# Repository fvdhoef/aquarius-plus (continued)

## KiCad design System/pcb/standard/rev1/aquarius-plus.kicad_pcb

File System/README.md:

# Aquarius+ System
This directory contains:
- [Schematic and PCB](pcb/)
- [FPGA firmware](fpga_cores/)
- [ESP32 firmware](esp32/)
- [ROM extensions source code](rom_src/aqplus_rom/)
- [Emulator source code](emulator/)
- [Documentation](docs/)

And some other stuff not mentioned in the list.

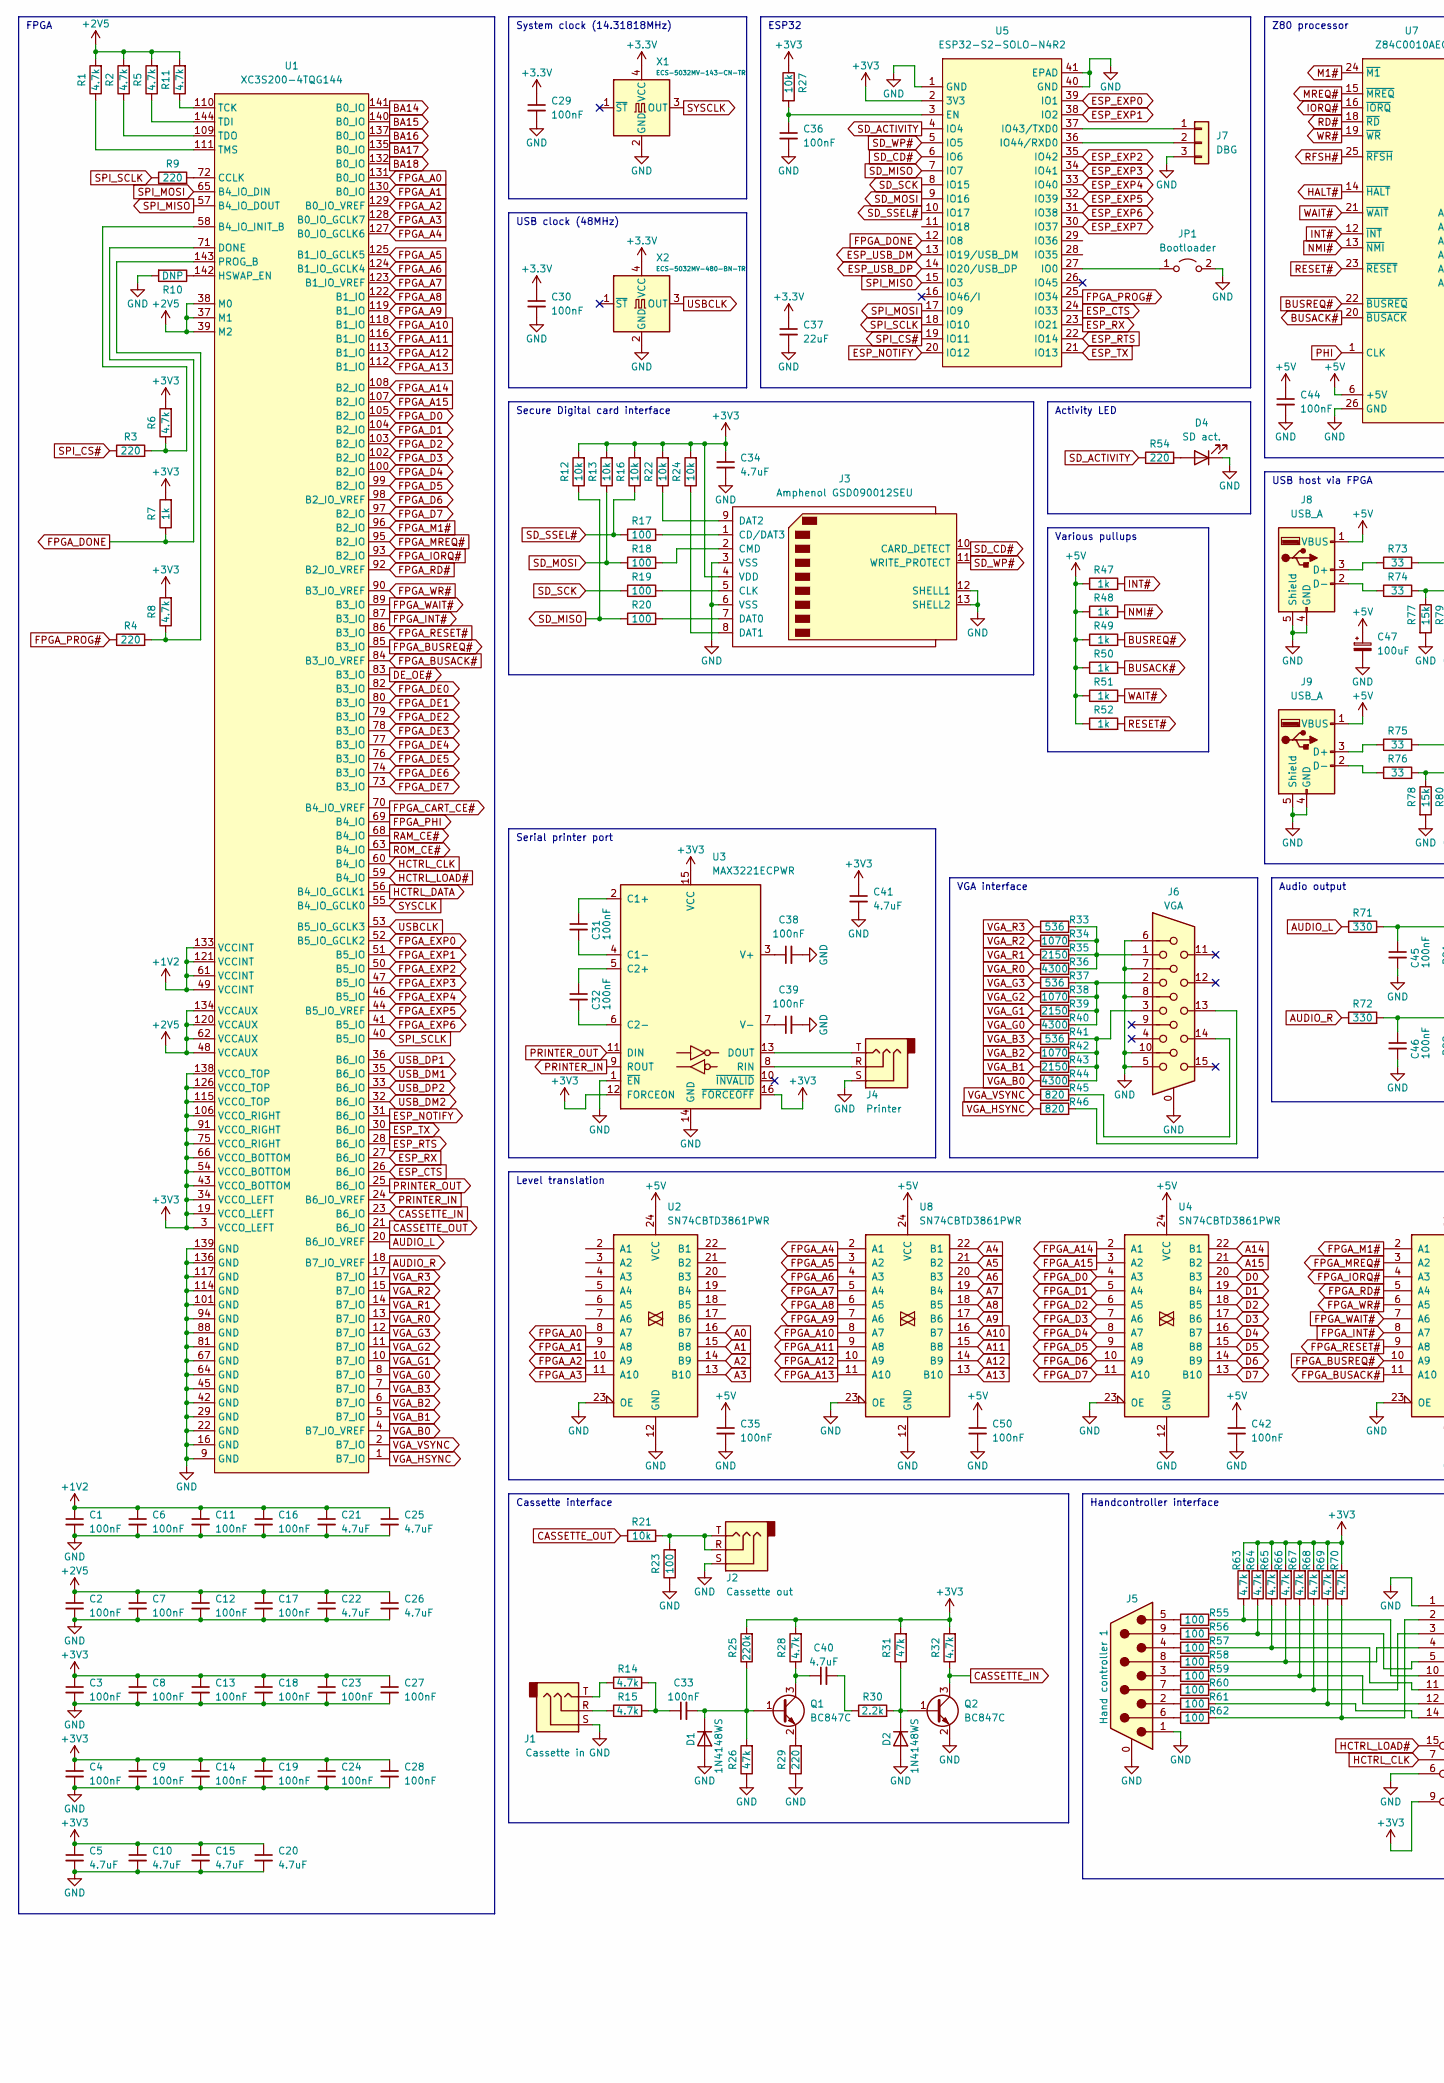
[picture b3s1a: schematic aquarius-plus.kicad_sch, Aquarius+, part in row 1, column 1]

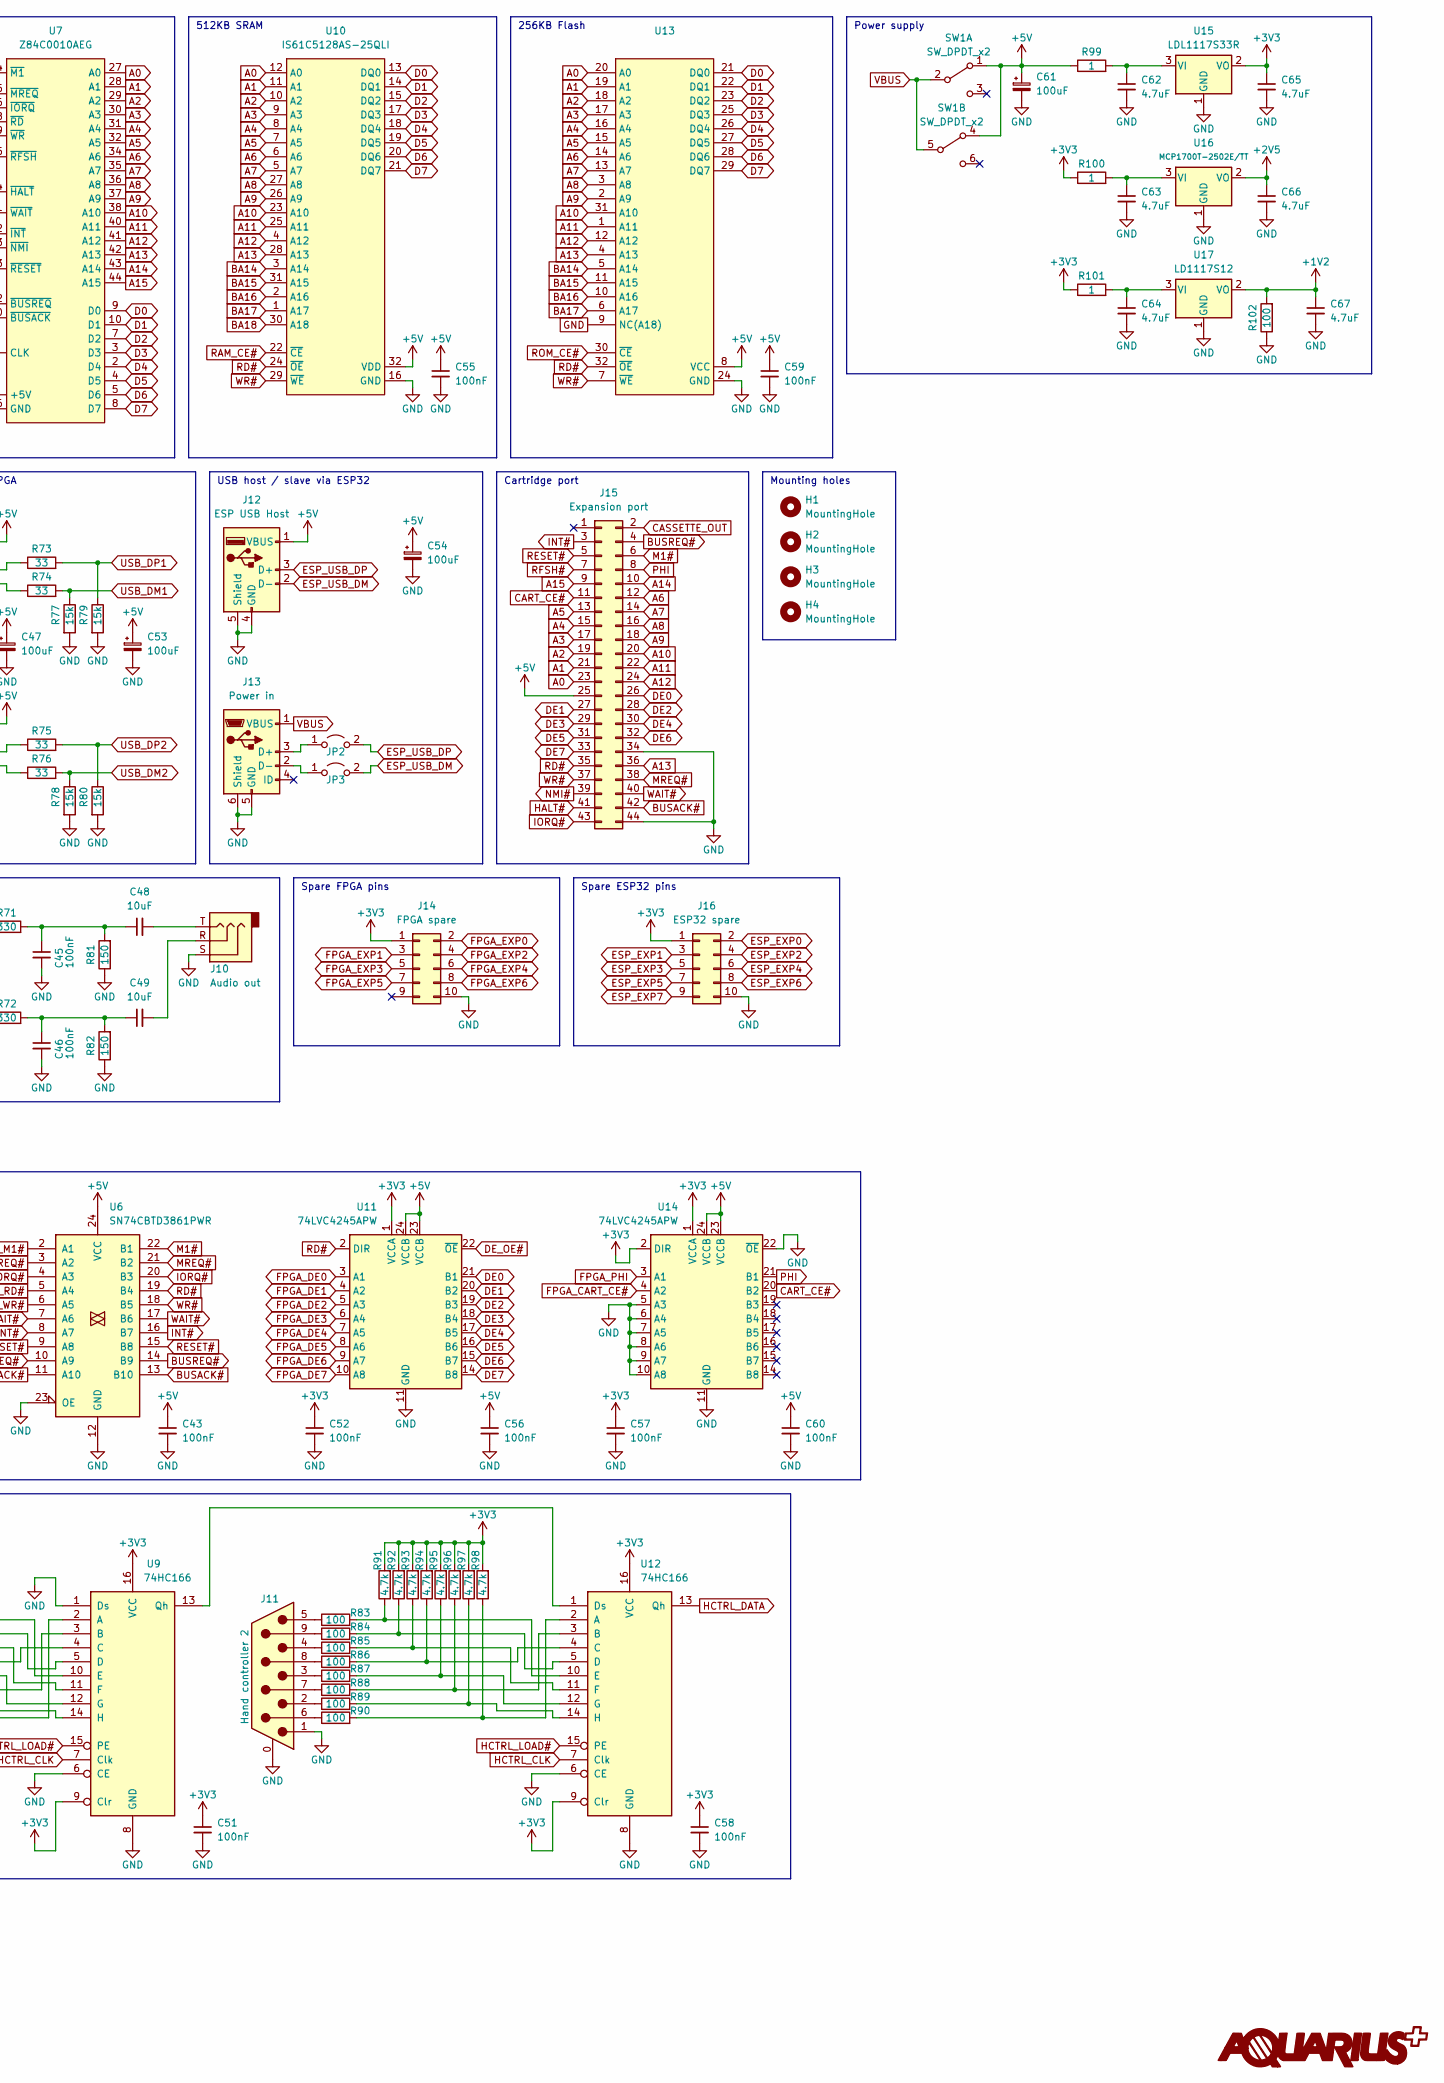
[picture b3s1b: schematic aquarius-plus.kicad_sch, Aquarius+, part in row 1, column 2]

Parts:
C1, C2, C3, C4, C6, C7, C8, C9, C11, C12, C13, C14, C16, C17, C18, C19, C23, C24, C27, C28, C29, C30, C31, C32, C33, C35, C36, C38, C39, C42, C43, C44, C45, C46, C50, C51, C52, C55, C56, C57, C58, C59, C60: 100nF; C_0603_1608Metric
C5, C10, C15, C20, C21, C22, C25, C26, C34, C40, C41, C62, C63, C64, C65, C66, C67: 4.7uF; C_0603_1608Metric
C37: 22uF; C_1206_3216Metric
C47, C53, C54, C61: 100uF; CP_Elec_6.3x7.7
C48, C49: 10uF; C_0805_2012Metric
D1, D2: 1N4148WS; D_SOD-323_HandSoldering
D4: SD act.; LED_D3.0mm_Horizontal_O1.27mm_Z2.0mm
H1, H2, H3, H4: MountingHole; MountingHole_3.2mm_M3
J1: Cassette in; Jack_3.5mm_CUI_SJ-3523-SMT_Horizontal
J2: Cassette out; Jack_3.5mm_CUI_SJ-3523-SMT_Horizontal
J3: Amphenol GSD090012SEU; SD_TE_2041021
J4: Printer; Jack_3.5mm_CUI_SJ-3523-SMT_Horizontal
J5: Hand controller 1; DSUB-9_Male_Horizontal_P2.77x2.84mm_EdgePinOffset9.90mm_Hou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
J6: VGA; ICD15S13E4GV00LF
J7: DBG; PinHeader_1x03_P2.54mm_Vertical
J8, J9: USB_A; USB_A_Molex_67643_Horizontal
J10: Audio out; Jack_3.5mm_CUI_SJ-3523-SMT_Horizontal
J11: Hand controller 2; DSUB-9_Male_Horizontal_P2.77x2.84mm_EdgePinOffset9.90mm_Hou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
J12: ESP USB Host; USB_A_Molex_67643_Horizontal
J13: Power in; 10118193-0001LF
J14: FPGA spare; PinHeader_2x05_P2.54mm_Vertical
J15: Expansion port; CR22A-44D-2.54DSA(70)
J16: ESP32 spare; PinHeader_2x05_P2.54mm_Vertical
JP1: Bootloader; PinHeader_1x02_P2.54mm_Vertical
JP2, JP3: USB; PinHeader_1x02_P2.54mm_Vertical
Q1, Q2: BC847C; SOT-23
R1, R2, R5, R6, R8, R11, R14, R15, R28, R32, R63, R64, R65, R66, R67, R68, R69, R70, R91, R92, R93, R94, R95, R96, R97, R98: 4.7k; R_0603_1608Metric
R3, R4, R9, R29, R54: 220; R_0603_1608Metric
R7, R47, R48, R49, R50, R51, R52: 1k; R_0603_1608Metric
R10: DNP; R_0603_1608Metric
R12, R13, R16, R21, R22, R24, R27: 10k; R_0603_1608Metric
R17, R18, R19, R20, R23, R55, R56, R57, R58, R59, R60, R61, R62, R83, R84, R85, R86, R87, R88, R89, R90, R102: 100; R_0603_1608Metric
R25: 220k; R_0603_1608Metric
R26, R31: 47k; R_0603_1608Metric
R30: 2.2k; R_0603_1608Metric
R33, R37, R41: 536; R_0603_1608Metric
R34, R38, R42: 1070; R_0603_1608Metric
R35, R39, R43: 2150; R_0603_1608Metric
R36, R40, R44: 4300; R_0603_1608Metric
R45, R46: 820; R_0603_1608Metric
R71, R72: 330; R_0603_1608Metric
R73, R74, R75, R76: 33; R_0603_1608Metric
R77, R78, R79, R80: 15k; R_0603_1608Metric
R81, R82: 150; R_0603_1608Metric
R99, R100, R101: 1; R_0603_1608Metric
SW1: SW_DPDT_x2; SW_E-Switch_EG2219_DPDT_Angled
U1: XC3S200-4TQG144; TQFP-144_20x20mm_P0.5mm
U2, U4, U6, U8: SN74CBTD3861PWR; TSSOP-24_4.4x7.8mm_P0.65mm
U3: MAX3221ECPWR; TSSOP-16_4.4x5mm_P0.65mm
U5: ESP32-S2-SOLO-N4R2
U7: Z84C0010AEG; LQFP-44_10x10mm_P0.8mm
U9, U12: 74HC166; SOIC-16_3.9x9.9mm_P1.27mm
U10: IS61C5128AS-25QLI; SSOP-32_11.305x20.495mm_P1.27mm
U11, U14: 74LVC4245APW; TSSOP-24_4.4x7.8mm_P0.65mm
U13: (no value)
U15: LDL1117S33R; SOT-223-3_TabPin2
U16: MCP1700T-2502E/TT; SOT-23
U17: LD1117S12; SOT-223-3_TabPin2
X1: ECS-5032MV-143-CN-TR; Oscillator_SMD_SeikoEpson_SG8002LB-4Pin_5.0x3.2mm
X2: ECS-5032MV-480-BN-TR; Oscillator_SMD_SeikoEpson_SG8002LB-4Pin_5.0x3.2mm

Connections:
+1V2: C1.1, C6.1, C11.1, C16.1, C21.1, C25.1, C67.1, R102.2, U1.49 (VCCINT), U1.61 (VCCINT), U1.121 (VCCINT), U1.133 (VCCINT), U17.2 (VO)
+2V5: C2.1, C7.1, C12.1, C17.1, C22.1, C26.1, C66.1, R1.2, R2.2, R5.2, R11.2, U1.37 (M1), U1.38 (M0), U1.39 (M2), U1.48 (VCCAUX), U1.62 (VCCAUX), U1.120 (VCCAUX), U1.134 (VCCAUX), U16.2 (VO)
+5V: C35.1, C42.1, C43.1, C44.1, C47.1, C50.1, C53.1, C54.1, C55.1, C56.1, C59.1, C60.1, C61.1, J8.1 (VBUS), J9.1 (VBUS), J12.1 (VBUS), J15.25, R47.1, R48.1, R49.1, R50.1, R51.1, R52.1, R99.1, SW1.1 (A), SW1.4 (A), U2.24 (VCC), U4.24 (VCC), U6.24 (VCC), U7.6 (+5V), U8.24 (VCC), U10.32 (VDD), U11.23 (VCCB), U11.24 (VCCB), U13.8 (VCC), U14.23 (VCCB), U14.24 (VCCB)
A0: J15.23, U2.16 (B7), U7.27 (A0), U10.12 (A0), U13.20 (A0)
A1: J15.21, U2.15 (B8), U7.28 (A1), U10.11 (A1), U13.19 (A1)
A2: J15.19, U2.14 (B9), U7.29 (A2), U10.10 (A2), U13.18 (A2)
A3: J15.17, U2.13 (B10), U7.30 (A3), U10.9 (A3), U13.17 (A3)
A4: J15.15, U7.31 (A4), U8.22 (B1), U10.8 (A4), U13.16 (A4)
A5: J15.13, U7.32 (A5), U8.21 (B2), U10.7 (A5), U13.15 (A5)
A6: J15.12, U7.34 (A6), U8.20 (B3), U10.6 (A6), U13.14 (A6)
A7: J15.14, U7.35 (A7), U8.19 (B4), U10.5 (A7), U13.13 (A7)
A8: J15.16, U7.36 (A8), U8.18 (B5), U10.27 (A8), U13.3 (A8)
A9: J15.18, U7.37 (A9), U8.17 (B6), U10.26 (A9), U13.2 (A9)
A10: J15.20, U7.38 (A10), U8.16 (B7), U10.23 (A10), U13.31 (A10)
A11: J15.22, U7.40 (A11), U8.15 (B8), U10.25 (A11), U13.1 (A11)
A12: J15.24, U7.41 (A12), U8.14 (B9), U10.4 (A12), U13.12 (A12)
A13: J15.36, U7.42 (A13), U8.13 (B10), U10.28 (A13), U13.4 (A13)
A14: J15.10, U4.22 (B1), U7.43 (A14)
A15: J15.9, U4.21 (B2), U7.44 (A15)
AUDIO_L: R71.1, U1.20 (B6_IO_VREF)
AUDIO_R: R72.1, U1.18 (B7_IO_VREF)
BA14: U1.141 (B0_IO), U10.3 (A14), U13.5 (A14)
BA15: U1.140 (B0_IO), U10.31 (A15), U13.11 (A15)
BA16: U1.137 (B0_IO), U10.2 (A16), U13.10 (A16)
BA17: U1.135 (B0_IO), U10.1 (A17), U13.6 (A17)
BA18: U1.132 (B0_IO), U10.30 (A18)
BUSACK#: J15.42, R50.2, U6.13 (B10), U7.20 (~BUSACK)
BUSREQ#: J15.4, R49.2, U6.14 (B9), U7.22 (~BUSREQ)
CART_CE#: J15.11, U14.20 (B2)
CASSETTE_IN: Q2.3 (C), R32.1, U1.23 (B6_IO)
CASSETTE_OUT: J15.2, R21.1, U1.21 (B6_IO)
D0: U4.20 (B3), U7.9 (D0), U10.13 (DQ0), U13.21 (DQ0)
D1: U4.19 (B4), U7.10 (D1), U10.14 (DQ1), U13.22 (DQ1)
D2: U4.18 (B5), U7.7 (D2), U10.15 (DQ2), U13.23 (DQ2)
D3: U4.17 (B6), U7.3 (D3), U10.17 (DQ3), U13.25 (DQ3)
D4: U4.16 (B7), U7.2 (D4), U10.18 (DQ4), U13.26 (DQ4)
D5: U4.15 (B8), U7.4 (D5), U10.19 (DQ5), U13.27 (DQ5)
D6: U4.14 (B9), U7.5 (D6), U10.20 (DQ6), U13.28 (DQ6)
D7: U4.13 (B10), U7.8 (D7), U10.21 (DQ7), U13.29 (DQ7)
DE0: J15.26, U11.21 (B1)
DE1: J15.27, U11.20 (B2)
DE2: J15.28, U11.19 (B3)
DE3: J15.29, U11.18 (B4)
DE4: J15.30, U11.17 (B5)
DE5: J15.31, U11.16 (B6)
DE6: J15.32, U11.15 (B7)
DE7: J15.33, U11.14 (B8)
DE_OE#: U1.83 (B3_IO), U11.22 (~OE)
ESP_CTS: U1.26 (B6_IO), U5.24 (IO33)
ESP_EXP0: J16.2, U5.39 (IO1)
ESP_EXP1: J16.3, U5.38 (IO2)
ESP_EXP2: J16.4, U5.35 (IO42)
ESP_EXP3: J16.5, U5.34 (IO41)
ESP_EXP4: J16.6, U5.33 (IO40)
ESP_EXP5: J16.7, U5.32 (IO39)
ESP_EXP6: J16.8, U5.31 (IO38)
ESP_EXP7: J16.9, U5.30 (IO37)
ESP_NOTIFY: U1.31 (B6_IO), U5.20 (IO12)
ESP_RTS: U1.28 (B6_IO), U5.22 (IO14)
ESP_RX: U1.27 (B6_IO), U5.23 (IO21)
ESP_TX: U1.30 (B6_IO), U5.21 (IO13)
ESP_USB_DM: J12.2 (D-), JP3.2 (B), U5.13 (IO19/USB_DM)
ESP_USB_DP: J12.3 (D+), JP2.2 (B), U5.14 (IO20/USB_DP)
FPGA_A0: U1.131 (B0_IO), U2.8 (A7)
FPGA_A1: U1.130 (B0_IO), U2.9 (A8)
FPGA_A2: U1.129 (B0_IO_VREF), U2.10 (A9)
FPGA_A3: U1.128 (B0_IO_GCLK7), U2.11 (A10)
FPGA_A4: U1.127 (B0_IO_GCLK6), U8.2 (A1)
FPGA_A5: U1.125 (B1_IO_GCLK5), U8.3 (A2)
FPGA_A6: U1.124 (B1_IO_GCLK4), U8.4 (A3)
FPGA_A7: U1.123 (B1_IO_VREF), U8.5 (A4)
FPGA_A8: U1.122 (B1_IO), U8.6 (A5)
FPGA_A9: U1.119 (B1_IO), U8.7 (A6)
FPGA_A10: U1.118 (B1_IO), U8.8 (A7)
FPGA_A11: U1.116 (B1_IO), U8.9 (A8)
FPGA_A12: U1.113 (B1_IO), U8.10 (A9)
FPGA_A13: U1.112 (B1_IO), U8.11 (A10)
FPGA_A14: U1.108 (B2_IO), U4.2 (A1)
FPGA_A15: U1.107 (B2_IO), U4.3 (A2)
FPGA_BUSACK#: U1.84 (B3_IO_VREF), U6.11 (A10)
FPGA_BUSREQ#: U1.85 (B3_IO), U6.10 (A9)
FPGA_CART_CE#: U1.70 (B4_IO_VREF), U14.4 (A2)
FPGA_D0: U1.105 (B2_IO), U4.4 (A3)
FPGA_D1: U1.104 (B2_IO), U4.5 (A4)
FPGA_D2: U1.103 (B2_IO), U4.6 (A5)
FPGA_D3: U1.102 (B2_IO), U4.7 (A6)
FPGA_D4: U1.100 (B2_IO), U4.8 (A7)
FPGA_D5: U1.99 (B2_IO), U4.9 (A8)
FPGA_D6: U1.98 (B2_IO_VREF), U4.10 (A9)
FPGA_D7: U1.97 (B2_IO), U4.11 (A10)
FPGA_DE0: U1.82 (B3_IO), U11.3 (A1)
FPGA_DE1: U1.80 (B3_IO), U11.4 (A2)
FPGA_DE2: U1.79 (B3_IO), U11.5 (A3)
FPGA_DE3: U1.78 (B3_IO), U11.6 (A4)
FPGA_DE4: U1.77 (B3_IO), U11.7 (A5)
FPGA_DE5: U1.76 (B3_IO), U11.8 (A6)
FPGA_DE6: U1.74 (B3_IO), U11.9 (A7)
FPGA_DE7: U1.73 (B3_IO), U11.10 (A8)
FPGA_DONE: R7.1, U1.71 (DONE), U5.12 (IO8)
FPGA_EXP0: J14.2, U1.52 (B5_IO_GCLK2)
FPGA_EXP1: J14.3, U1.51 (B5_IO)
FPGA_EXP2: J14.4, U1.50 (B5_IO)
FPGA_EXP3: J14.5, U1.47 (B5_IO)
FPGA_EXP4: J14.6, U1.46 (B5_IO)
FPGA_EXP5: J14.7, U1.44 (B5_IO_VREF)
FPGA_EXP6: J14.8, U1.41 (B5_IO)
FPGA_INT#: U1.87 (B3_IO), U6.8 (A7)
FPGA_IORQ#: U1.93 (B2_IO), U6.4 (A3)
FPGA_M1#: U1.96 (B2_IO), U6.2 (A1)
FPGA_MREQ#: U1.95 (B2_IO), U6.3 (A2)
FPGA_PHI: U1.69 (B4_IO), U14.3 (A1)
FPGA_PROG#: R4.1, U5.25 (IO34)
FPGA_RD#: U1.92 (B2_IO_VREF), U6.5 (A4)
FPGA_RESET#: U1.86 (B3_IO), U6.9 (A8)
FPGA_WAIT#: U1.89 (B3_IO), U6.7 (A6)
FPGA_WR#: U1.90 (B3_IO_VREF), U6.6 (A5)
GND: C1.2, C2.2, C3.2, C4.2, C5.2, C6.2, C7.2, C8.2, C9.2, C10.2, C11.2, C12.2, C13.2, C14.2, C15.2, C16.2, C17.2, C18.2, C19.2, C20.2, C21.2, C22.2, C23.2, C24.2, C25.2, C26.2, C27.2, C28.2, C29.2, C30.2, C34.2, C35.2, C36.2, C37.2, C38.2, C39.2, C41.2, C42.2, C43.2, C44.2, C45.2, C46.2, C47.2, C50.2, C51.2, C52.2, C53.2, C54.2, C55.2, C56.2, C57.2, C58.2, C59.2, C60.2, C61.2, C62.2, C63.2, C64.2, C65.2, C66.2, C67.2, D1.2 (A), D2.2 (A), D4.1 (K), J1.S, J2.S, J3.3 (VSS), J3.6 (VSS), J3.12 (SHELL1), J3.13 (SHELL2), J4.S, J5.0 (PAD), J5.1, J6.0, J6.5, J6.6, J6.7, J6.8, J6.10, J7.3, J8.4 (GND), J8.5 (Shield), J9.4 (GND), J9.5 (Shield), J10.S, J11.0 (PAD), J11.1, J12.4 (GND), J12.5 (Shield), J13.5 (GND), J13.6 (Shield), J14.10, J15.34, J15.44, J16.10, JP1.2 (B), Q2.2 (E), R10.2, R23.1, R26.1, R29.1, R77.2, R78.2, R79.2, R80.2, R81.1, R82.1, R102.1, U1.9 (GND), U1.16 (GND), U1.22 (GND), U1.29 (GND), U1.42 (GND), U1.45 (GND), U1.64 (GND), U1.67 (GND), U1.81 (GND), U1.88 (GND), U1.94 (GND), U1.101 (GND), U1.114 (GND), U1.117 (GND), U1.136 (GND), U1.139 (GND), U2.12 (GND), U2.23 (OE), U3.1 (~EN), U3.14 (GND), U4.12 (GND), U4.23 (OE), U5.1 (GND), U5.40 (GND), U5.41 (EPAD), U6.12 (GND), U6.23 (OE), U7.26 (GND), U8.12 (GND), U8.23 (OE), U9.1 (Ds), U9.6 (CE), U9.8 (GND), U10.16 (GND), U11.11 (GND), U11.12 (GND), U11.13 (GND), U12.6 (CE), U12.8 (GND), U13.9 (NC(A18)), U13.24 (GND), U14.5 (A3), U14.6 (A4), U14.7 (A5), U14.8 (A6), U14.9 (A7), U14.10 (A8), U14.11 (GND), U14.12 (GND), U14.13 (GND), U14.22 (~OE), U15.1 (GND), U16.1 (GND), U17.1 (GND), X1.2 (GND), X2.2 (GND)
HALT#: J15.41, U7.14 (~HALT)
HCTRL_CLK: U1.60 (B4_IO), U9.7 (Clk), U12.7 (Clk)
HCTRL_DATA: U1.56 (B4_IO_GCLK1), U12.13 (Qh)
HCTRL_LOAD#: U1.59 (B4_IO), U9.15 (PE), U12.15 (PE)
INT#: J15.3, R47.2, U6.16 (B7), U7.12 (~INT)
IORQ#: J15.43, U6.20 (B3), U7.16 (~IORQ)
M1#: J15.6, U6.22 (B1), U7.24 (~M1)
MREQ#: J15.38, U6.21 (B2), U7.15 (~MREQ)
NMI#: J15.39, R48.2, U7.13 (~NMI)
unnamed: C31.1, U3.2 (C1+)
unnamed: C31.2, U3.4 (C1-)
unnamed: C32.1, U3.5 (C2+)
unnamed: C32.2, U3.6 (C2-)
unnamed: C33.1, R14.2, R15.2
unnamed: C33.2, D1.1 (K), Q1.1 (B), R25.1, R26.2
unnamed: C36.1, R27.2, U5.3 (EN)
unnamed: C38.1, U3.3 (V+)
unnamed: C39.1, U3.7 (V-)
unnamed: C40.1, Q1.3 (C), R28.1
unnamed: C40.2, R30.1
unnamed: C45.1, C48.1, R71.2, R81.2
unnamed: C46.1, C49.1, R72.2, R82.2
unnamed: C48.2, J10.T
unnamed: C49.2, J10.R
unnamed: C62.1, R99.2, U15.3 (VI)
unnamed: C63.1, R100.2, U16.3 (VI)
unnamed: C64.1, R101.2, U17.3 (VI)
unnamed: D2.1 (K), Q2.1 (B), R30.2, R31.1
unnamed: D4.2 (A), R54.2
unnamed: J1.R, R15.1
unnamed: J1.T, R14.1
unnamed: J2.R, J2.T, R21.2, R23.2
unnamed: J3.1 (CD/DAT3), R17.2
unnamed: J3.2 (CMD), R18.2
unnamed: J3.5 (CLK), R19.2
unnamed: J3.7 (DAT0), R20.2
unnamed: J3.8 (DAT1), R24.1
unnamed: J3.9 (DAT2), R22.1
unnamed: J4.R, U3.8 (RIN)
unnamed: J4.T, U3.13 (DOUT)
unnamed: J5.2, R61.1
unnamed: J5.3, R59.1
unnamed: J5.4, R57.1
unnamed: J5.5, R55.1
unnamed: J5.6, R62.1
unnamed: J5.7, R60.1
unnamed: J5.8, R58.1
unnamed: J5.9, R56.1
unnamed: J6.1, R33.2, R34.2, R35.2, R36.2
unnamed: J6.2, R37.2, R38.2, R39.2, R40.2
unnamed: J6.3, R41.2, R42.2, R43.2, R44.2
unnamed: J6.13, R46.2
unnamed: J6.14, R45.2
unnamed: J7.1, U5.37 (IO43/TXD0)
unnamed: J7.2, U5.36 (IO44/RXD0)
unnamed: J8.2 (D-), R74.1
unnamed: J8.3 (D+), R73.1
unnamed: J9.2 (D-), R76.1
unnamed: J9.3 (D+), R75.1
unnamed: J11.2, R89.1
unnamed: J11.3, R87.1
unnamed: J11.4, R85.1
unnamed: J11.5, R83.1
unnamed: J11.6, R90.1
unnamed: J11.7, R88.1
unnamed: J11.8, R86.1
unnamed: J11.9, R84.1
unnamed: J13.2 (D-), JP3.1 (A)
unnamed: J13.3 (D+), JP2.1 (A)
unnamed: JP1.1 (A), U5.27 (IO0)
unnamed: Q1.2 (E), R29.2
unnamed: R1.1, U1.111 (TMS)
unnamed: R2.1, U1.109 (TDO)
unnamed: R3.2, R6.1, U1.58 (B4_IO_INIT_B)
unnamed: R4.2, R8.1, U1.143 (PROG_B)
unnamed: R5.1, U1.144 (TDI)
unnamed: R9.2, U1.72 (CCLK)
unnamed: R10.1, U1.142 (HSWAP_EN)
unnamed: R11.1, U1.110 (TCK)
unnamed: R55.2, R63.1, U9.10 (E)
unnamed: R56.2, R64.1, U9.5 (D)
unnamed: R57.2, R65.1, U9.11 (F)
unnamed: R58.2, R66.1, U9.4 (C)
unnamed: R59.2, R67.1, U9.12 (G)
unnamed: R60.2, R68.1, U9.3 (B)
unnamed: R61.2, R69.1, U9.14 (H)
unnamed: R62.2, R70.1, U9.2 (A)
unnamed: R83.2, R91.1, U12.10 (E)
unnamed: R84.2, R92.1, U12.5 (D)
unnamed: R85.2, R93.1, U12.11 (F)
unnamed: R86.2, R94.1, U12.4 (C)
unnamed: R87.2, R95.1, U12.12 (G)
unnamed: R88.2, R96.1, U12.3 (B)
unnamed: R89.2, R97.1, U12.14 (H)
unnamed: R90.2, R98.1, U12.2 (A)
unnamed: U9.13 (Qh), U12.1 (Ds)
PHI: J15.8, U7.1 (CLK), U14.21 (B1)
PRINTER_IN: U1.24 (B6_IO_VREF), U3.9 (ROUT)
PRINTER_OUT: U1.25 (B6_IO), U3.11 (DIN)
RAM_CE#: U1.68 (B4_IO), U10.22 (~CE)
RD#: J15.35, U6.19 (B4), U7.18 (~RD), U10.24 (~OE), U11.2 (DIR), U13.32 (~OE)
RESET#: J15.5, R52.2, U6.15 (B8), U7.23 (~RESET)
RFSH#: J15.7, U7.25 (~RFSH)
ROM_CE#: U1.63 (B4_IO), U13.30 (~CE)
SD_ACTIVITY: R54.1, U5.4 (IO4)
SD_CD#: J3.10 (CARD_DETECT), U5.6 (IO6)
SD_MISO: R12.1, R20.1, U5.7 (IO7)
SD_MOSI: R13.1, R18.1, U5.9 (IO16)
SD_SCK: R19.1, U5.8 (IO15)
SD_SSEL#: R16.1, R17.1, U5.10 (IO17)
SD_WP#: J3.11 (WRITE_PROTECT), U5.5 (IO5)
SPI_CS#: R3.1, U5.19 (IO11)
SPI_MISO: U1.57 (B4_IO_DOUT), U5.15 (IO3)
SPI_MOSI: U1.65 (B4_IO_DIN), U5.17 (IO9)
SPI_SCLK: R9.1, U1.40 (B5_IO), U5.18 (IO10)
SYSCLK: U1.55 (B4_IO_GCLK0), X1.3 (OUT)
USBCLK: U1.53 (B5_IO_GCLK3), X2.3 (OUT)
USB_DM1: R74.2, R77.1, U1.35 (B6_IO)
USB_DM2: R76.2, R78.1, U1.32 (B6_IO)
USB_DP1: R73.2, R79.1, U1.36 (B6_IO)
USB_DP2: R75.2, R80.1, U1.33 (B6_IO)
VBUS: J13.1 (VBUS), SW1.2 (B), SW1.5 (B)
VGA_B0: R44.1, U1.4 (B7_IO_VREF)
VGA_B1: R43.1, U1.5 (B7_IO)
VGA_B2: R42.1, U1.6 (B7_IO)
VGA_B3: R41.1, U1.7 (B7_IO)
VGA_G0: R40.1, U1.8 (B7_IO)
VGA_G1: R39.1, U1.10 (B7_IO)
VGA_G2: R38.1, U1.11 (B7_IO)
VGA_G3: R37.1, U1.12 (B7_IO)
VGA_HSYNC: R46.1, U1.1 (B7_IO)
VGA_R0: R36.1, U1.13 (B7_IO)
VGA_R1: R35.1, U1.14 (B7_IO)
VGA_R2: R34.1, U1.15 (B7_IO)
VGA_R3: R33.1, U1.17 (B7_IO)
VGA_VSYNC: R45.1, U1.2 (B7_IO)
WAIT#: J15.40, R51.2, U6.17 (B6), U7.21 (~WAIT)
WR#: J15.37, U6.18 (B5), U7.19 (~WR), U10.29 (~WE), U13.7 (~WE)

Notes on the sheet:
Level translation
System clock (14.31818MHz)
USB host / slave via ESP32
USB clock (48MHz)
Various pullups
Audio output
Activity LED
Cartridge port
Serial printer port
Power supply
Spare FPGA pins
Cassette interface
ESP32
256KB Flash
512KB SRAM
Z80 processor
FPGA
Spare ESP32 pins
VGA interface
Mounting holes
Secure Digital card interface
USB host via FPGA
Handcontroller interface

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
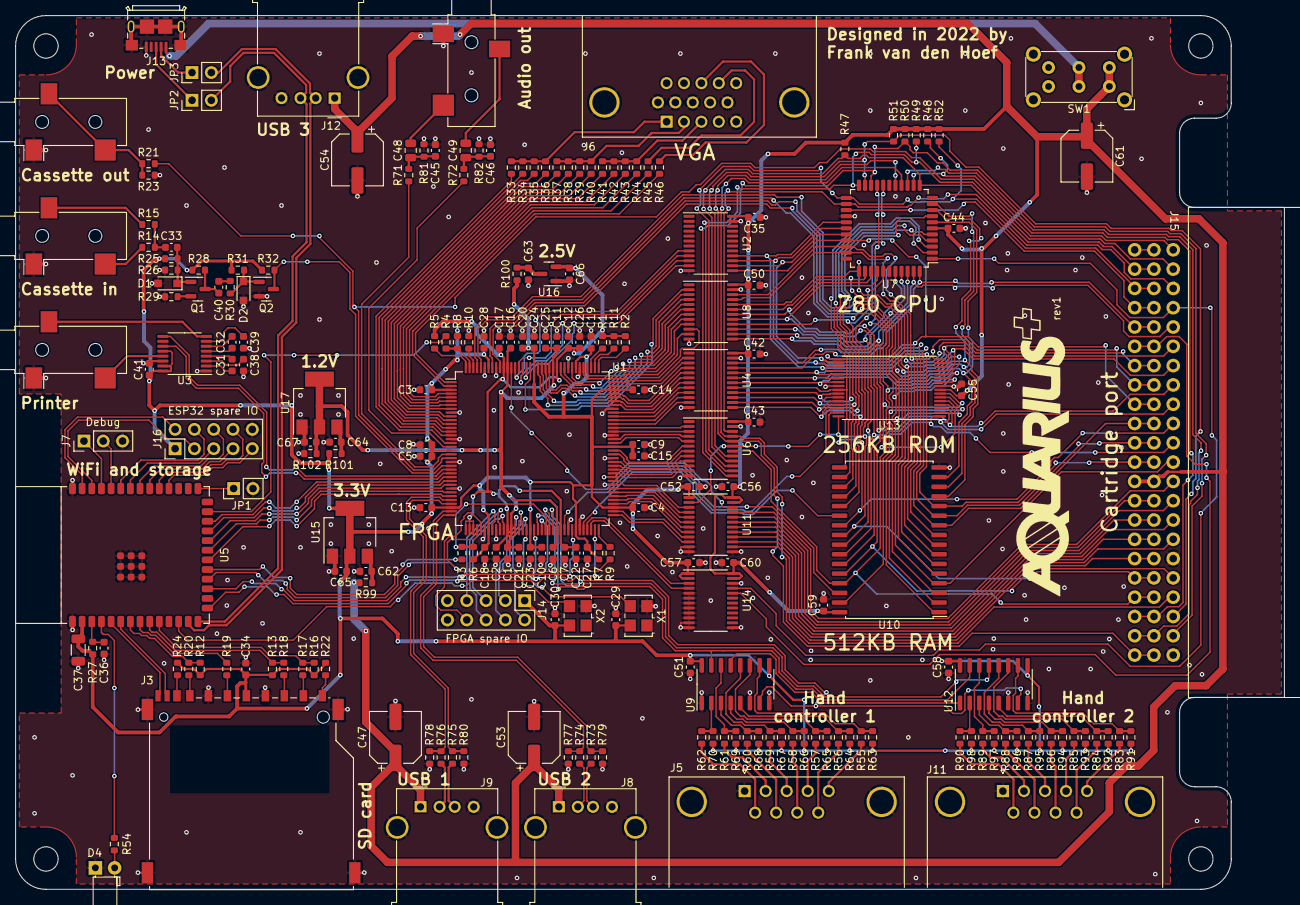
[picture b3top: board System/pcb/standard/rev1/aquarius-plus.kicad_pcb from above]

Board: 2 copper layers, 167.0 x 115.0 mm, 216 parts (0 on the bottom side), 256 nets.

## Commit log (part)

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2024-02-10 plusBASIC to v0.21j
2024-02-10 Revert "GitIgnore Updates"
    This reverts commit 9f1a4188bdc0e5a5db3d49bdede67cb49d142882.
2024-02-10 Updating romfs.
2024-02-10 Updating workflow.
2024-02-11 Committing romfs.bin
2024-02-12 Post V0.24 sdcard updates
2024-02-13 Various Updates
2024-02-13 plusBASIC to v0.21q
2024-02-19 Updates to TheValley & rev2 BOM
2024-02-20 PCB Mini Updates
2024-02-21 Screenshot save option
2024-02-21 plusBASIC to v0.21v
2024-02-21 Add lodepng
2024-02-21 Add <array>
2024-02-21 Fixing vs project
2024-02-22 cpm disks
2024-02-24 Fixing screenshot functionality for windows.
2024-02-24 plusBASIC to v0.21w
2024-02-24 updategh: automatic detection of latest tag, fixes #71
2024-02-24 Bom and stuff
2024-02-24 Housekeeping
2024-02-24 Read-me tweaks
2024-02-26 Adding license file.
2024-02-27 Include Turmoil ROM
2024-03-07 plusBASIC to V0.22c
2024-03-17 Fixing compilation issue on esp-idf v5.2.1
2024-03-17 ESP-IDF SDK config update for V5.2.1
2024-03-17 Removing code for no-longer functioning sysrom endpoint.
2024-03-17 Updating ESP-IDF version to V5.2.1
2024-03-19 Adding new github root certificate
2024-03-19 plusBASIC to V0.22g
2024-03-21 MFG Assembly Notes update
2024-03-30 Adding mobile form factor docs
2024-04-01 Fix for USE CHRSET syntax updates
2024-04-01 plusBASIC to v0.22k
2024-04-02 Added Horoscope to the demos folder
    Prerelease version, only runs Biorhythms.
2024-04-04 Added PCBWay option to Maker > PCB folder
2024-04-07 Adding extra root certificates to fix updategh.
2024-04-13 ISS-Map and Bitmaps2 demos updated
2024-04-19 Demo software updates
2024-04-23 plusBASIC to v0.22l
2024-05-01 Correcting the line at which the vblank interrupt in generated.
2024-05-01 Updating plusBASIC to v0.22m
2024-05-08 Updated MFG notes, and updated rev2 KiCAD Project file
2024-05-21 plusBASIC to v0.22w
2024-05-21 Proof of concept with t80a core works!
2024-06-01 Fixing warning when compiling on Linux
2024-06-02 TCP/IP support for windows emulator
2024-06-02 plusBASIC to v0.22x
2024-06-02 Implemented HTTP(S) support on Windows emulator.
2024-06-04 AQP rev2 Case Tweaks
    Make case more easily printable on FDM printers: use outline version of logo rather than recessed version.
2024-06-04 Update Mini Case
    Added images and updated case to allow for better FDM printing results.
2024-06-10 Updated ISS-Map demo to make use of SPLIT command for JSON
2024-06-17 Updates to ISS-Map demo
2024-07-14 Refactoring mouse code.
2024-07-14 Emulator game controller support.
2024-07-14 Added ESP_GETGAMECTRL command on emulator.
2024-07-18 Replacing esp-nimble-cpp with own code.
2024-07-20 Gamepad decoding.
2024-07-20 Update CI script.
2024-08-06 Switched to using bank 1 instead of 3 to load images.
2024-08-07 Better error handling for direnum. Fixes #82
2024-08-15 Fixing compatibility with GNU sed
2024-08-15 Switch to 40 columns mode. Fixes #84
2024-08-16 Add command line option to ignore 'halt' instruction.
2024-08-19 Rewrote image.bas to use plusBASIC commands
2024-08-21 Moved -i command-line option to Debug pulldown menu.
2024-08-22 Updated plusBASIC to v0.22y
2024-08-22 Fixing build issues on Windows.
2024-08-22 PCB Std rev3 Updates
2024-08-22 First pass at Mini rev1 (vZ)
2024-08-22 More Aq+ Mini vZ work...
2024-08-23 Mega PCB development
2024-08-26 Updated plusBASIC to v0.22y3
2024-08-26 plusBASIC v0.23
2024-08-26 Reorganize PCB folder by system class
2024-08-26 Mini vZ rev1
2024-08-26 Update PCB Archive tree
2024-08-26 Mini rev1 vZ Updates
2024-08-28 Mini vZ rev1 updates
2024-08-28 Std rev3 PCB Updates
2024-08-30 PCB folder updates and reorg
2024-08-31 pullup for printer_in on AQ+Mini
2024-08-31 More PCB tidying up
2024-09-02 Mini vZ PCB tweaks
2024-09-07 Updated SplashScreen demo to us BAS file
2024-09-18 Set all 4 palettes to default values on boot.
2024-09-23 Lots of updates...
    Added Aq+ ICON images.
    Reworked PCB directory.
    Changed Mega project to Moda.
    etc...
2024-09-23 More tweaking of Moda PCB (and new outline logo)
2024-09-24 Moda PCB updates
2024-09-28 Reorganizing files.
2024-09-28 Adding linter.
2024-09-28 Migrating code from morphbook.
2024-09-28 esp-idf to v5.3.1
2024-09-28 Cleaning up.
2024-09-28 Refactoring code.
2024-09-28 Fixes.
2024-09-28 Fixing UCF
2024-09-28 Working on adding display overlay.
2024-09-29 Display overlay.
2024-09-29 Working on display overlay.
2024-09-29 Changes.
2024-10-01 Refactoring.
2024-10-01 Working on menus
2024-10-01 Timezone selection. Video timing selection.
2024-10-01 Keyboard layout selection
2024-10-01 Mouse sensitivity setting.
2024-10-01 Update from github.
2024-10-01 SD card update.
2024-10-01 Version menu
2024-10-01 Fixing keyboard layouts and leds. Added version menu.
2024-10-01 Edit hostname.
2024-10-01 ESP stats menu
2024-10-02 Cleanup.
2024-10-02 Fixing windows build.
2024-10-02 Removing settings app.
2024-10-02 Updating plusBASIC
2024-10-02 Adding T80 core.
2024-10-03 Working on T80 integration.
2024-10-03 T80 core working.
2024-10-03 Enabling pull up on reset pin.
2024-10-03 Force turbo option.
2024-10-03 Message on external Z80 toggle.
2024-10-03 Adding full root certificates.
2024-10-03 Preliminary ble keyboard support.
2024-10-03 Moda PCB tweaks.
2024-10-05 Option to toggle file server on/off
2024-10-05 Fixed http keyboard typing.
2024-10-05 Implemented file compression for FPGA image and SSL certificates.
2024-10-05 Loading other cores.
2024-10-05 Unifying code.
2024-10-06 Standard PCB rev3 updates in anticipation of prototype build
2024-10-06 Option to automatically bypass start screen.
2024-10-06 Restoring SPI bus master interface.
2024-10-06 Added options for screenshot and dump cartridge.
2024-10-06 ROM descrambling tool
2024-10-06 Improved string editor.
2024-10-06 Improved menu.
2024-10-08 Updates.
2024-10-12 Bluetooth and HID fixes.
2024-10-12 Updating for new ESP ROM.
2024-10-12 Cleaning up
2024-10-12 Reorganizing.
2024-10-12 Working on aqms core.
2024-10-13 Refactoring. T80 support.
2024-10-13 Core info
2024-10-13 Adding core info.
2024-10-14 Demo updates...
2024-10-15 Fixing bus mastering on mini vZ
2024-10-15 Version info. Factory reset confirmation.
2024-10-15 Allow overlay menu to be controlled by game controller.
2024-10-15 Worked on gamepad mapping.
2024-10-17 Horoscope Updates
2024-10-17 Worked on gamepad/keyboard mappings.
2024-10-17 Updating readme.
2024-10-20 plusBASIC to v0.23k
2024-10-20 Fixing auto bypass.
2024-10-20 Leave forced turbo enabled on reset.
2024-10-20 Force turbo mode now persistent.
2024-10-20 Boot code fixes.
2024-10-20 Load/save presets for controller mappings.
2024-10-20 Show stars in password field.
2024-10-20 Adding some presets to sdcard.
2024-10-20 vZ Jumper Fix
2024-10-20 Demos folder updates
2024-10-20 Tools updates.
2024-10-20 Nest config files in esp32 folder
2024-10-20 Added util folder
2024-10-24 Linux fixes.
2024-10-24 Adding mDNS support.
2024-10-24 plusBASIC v0.23m
2024-10-24 Fix line endings.
2024-10-26 Fix for case-sensitive file systems.
2024-10-26 Added support for unlimited turbo.
2024-10-26 plusBASIC v0.23n
2024-10-27 Added jump point for plusBASIC to boot.bin Changed png2bm/image.bas and png2bm4bpp/image.bas to match updated LOAD DIR format
2024-10-29 Adding cold/warm boot functionality.
2024-11-02 Updating imgui.
2024-11-02 Fixing display issues on Linux.
2024-11-02 Cleaning up compile warning.
2024-11-02 Adding shortcuts for debugger keys.
2024-11-10 Case & PCB Updates
2024-11-14 Updated write.bat.
2024-11-16 Modified FPGA ROM to load boot.bin from SD card root directory if present.
2024-11-16 Updated rom binary.
2024-11-16 Startup ROM passes cold/warm boot flag to boot.bin in HL
2024-11-17 Adding missing GETGAMECTRL implementation.
2024-11-17 Fixed missing constant in fpgarom.asm
2024-11-17 Updating FPGA core (boot ROM)
2024-11-17 Modified boot.asm to check Warm Start flag and behave accordingly
2024-11-18 boot.bin copies enencrypted cart to page 63 and runs it from there
2024-11-18 Adding compressed bitfile.
2024-11-22 Artwork
2024-12-01 Updated plusBASIC
2024-12-14 Updated getsysrom.baq, added train demo
2024-12-15 Mini/vZ Updates
2024-12-15 Std Case Updates
2025-01-13 Modified CP/M to use the same page mapping as BASIC so Ctrl-Esc warm boot will restart CP/M instead of returning to BASIC.
2025-01-13 Debugged CP/M Ctrl-Esc restart
2025-01-17 Bugfix.
2025-01-17 plusBASIC to V0.23r.
2025-01-25 Bumped CP/M subversion to 1.1
2025-02-09 Fixing crash on pasting text.
2025-02-09 Updating root certificates. Updating ESP-IDF to 5.4.0
2025-02-09 Correcting ESP-IDF version.
2025-02-09 Allow toggling on/off menu items by pressing enter.
2025-02-09 Menu option to enable gamepad navigation.
2025-02-09 Reverting changes to fpgarom to fix boot issue.
2025-02-09 plusBASIC v0.23u
2025-02-09 Updated bas2baq.py and baq2bas.py to latest version
2025-02-09 Modified boot.asm to directly read IO_SYSCTRL to check for warm boot
2025-02-09 plusBASIC v0.23v
2025-02-09 Restored push/pop of IO_SYSCTRL, but reads form port at start
2025-02-09 plusBASIC v0.24
2025-02-09 plusBASIC v0.24a
2025-02-11 Adding 1+3+5 reset combo to AQMS. Fixing bug in AQMS menu system.
2025-03-08 Adding CMakeLists.txt
2025-03-08 Adding options to scale UI fonts.
2025-03-10 Small fixes.
2025-03-11 Putting FPGA in subdirectory.
2025-03-11 Initial bootrom.
2025-03-11 Removing unneeded CPU functionality.
2025-03-13 spiregs
2025-03-20 Working.
2025-03-20 Enabling hub support. Small bluetooth changes.
2025-03-20 plusBASIC v0.24g
2025-03-27 Fix for ESP UART receiving.
2025-03-27 plusBASIC 0.24h
2025-03-27 Switch to esp-idf v5.4 development branch until v5.4.1 comes out.
2025-03-27 Added ESP-IDF version to version menu.
2025-03-27 Fixing windows build. Removing installer project.
2025-03-27 Fixing.
2025-03-27 Implemented SRAM cache.
2025-03-29 Fixes for Windows / CMake
2025-03-29 Working on workflow for cmake.
2025-03-30 macOS CMake
2025-03-30 Adding windows installer.
2025-04-03 ESP-IDF v5.4.1
2025-04-05 Working on splitting up repo.
2025-04-05 Moved pcb folder into submodule.
2025-04-05 Moving SDK into submodule.
2025-04-05 Moving sdcard folder into submodule.
2025-04-05 Update submodule.
2025-04-05 Updating romfs generation.
2025-04-05 Checkout submodules.
2025-04-05 Updating submodule.
2025-04-05 Splitting up Github workflow.
2025-04-05 Renaming workflow.
2025-04-08 Sync changes
2025-04-14 Updated submodules.
2025-04-14 Fixing submodule reference.
2025-04-14 Update pcb
2025-04-14 Fixing versions on zip files.
2025-04-15 Updated submodule.
2025-04-16 Updated emulator.
2025-04-16 Updated emulator
2025-04-26 Updating submodules.
2025-04-26 Fixing version.
2025-06-22 Updated submodules, plusbasic.
2025-06-22 Removing wiki submodule due to windows build errors.
2025-06-22 Fixing windows warnings.
2025-06-22 Updated windows warning.
2025-06-23 Minor edit to create new tag.
2025-06-23 Tweaking build script.
2025-06-24 Compressed romfs.
2025-06-24 Include root certificates in romfs.
2025-07-02 Updating submodules. Updated firmware workflow.
2025-11-30 Updated submodules. ESP-IDF v5.5.1.
